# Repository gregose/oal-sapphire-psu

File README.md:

# oal-sapphire-psu
Transformer and rectifier board for RJM's Sapphire

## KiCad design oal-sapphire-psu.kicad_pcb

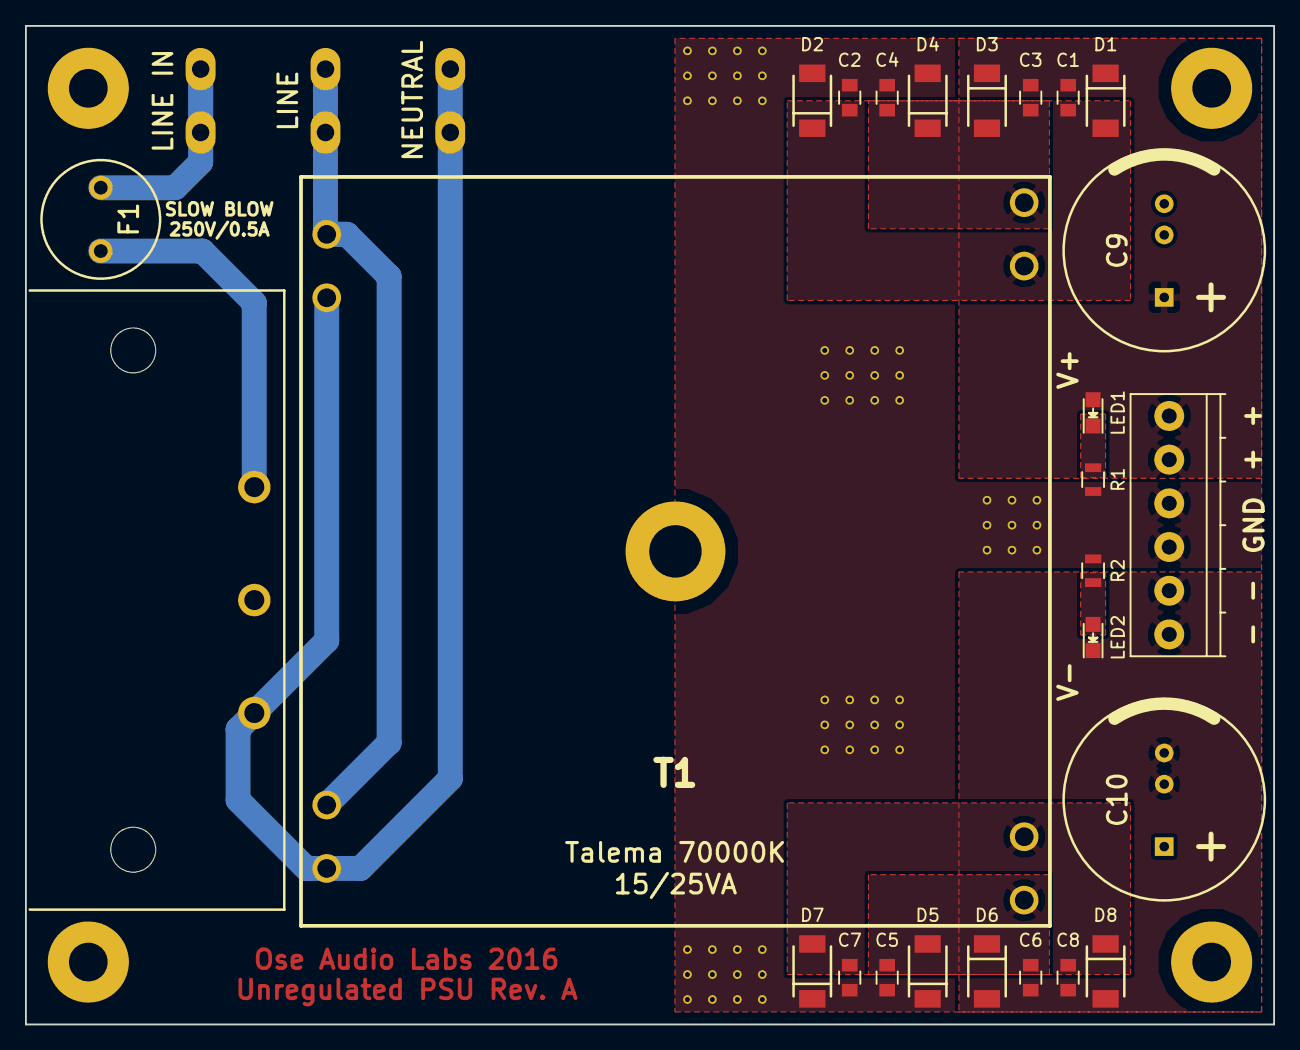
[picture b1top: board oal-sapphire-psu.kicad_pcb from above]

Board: 2 copper layers, 100.0 x 80.0 mm, 33 parts (0 on the bottom side), 13 nets.

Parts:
C1, C2, C3, C4, C5, C6, C7, C8: 0.1uF; C_0805
C9, C10: 4700uF; 25V-LYTIC-7.5-5-16mm
D1, D2, D3, D4, D5, D6, D7, D8: D; NXP-SOD128
F1: FUSE; SCHURTER_FMS250V
LED1: V+; LED_0805
LED2: V-; LED_0805
P1: 120V AC; Schurter_GSP1.8101.1
P2: LINE IN; FASTON_TAB
P3: LINE; FASTON_TAB
P4: NEUTRAL; FASTON_TAB
P7: OUTPUT; TerminalBlock_Pheonix_PT-3.5mm_6pol-Vertical
R1, R2: 680R; R_0805
T1: TALEMA-25VA/12V; TALEMA_70000K_15-25VA
X1, X2, X3, X4: MOUNTING_HOLE; MOUNTING_HOLE-M3

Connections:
GROUND: C2.1, C4.1, C5.2, C7.2, C9.2, C10.1, D2.2, D4.2, D5.1, D7.1, P7.3, P7.4, R1.1, R2.2
LINE: F1.1, P1.1
NEUTRAL: P1.3, P4.1, T1.3, T1.5
unnamed: C1.1, C2.2, D1.2, D2.1, T1.12
unnamed: C3.1, C4.2, D3.2, D4.1, T1.11
unnamed: C5.1, C6.2, D5.2, D6.1, T1.14
unnamed: C7.1, C8.2, D7.2, D8.1, T1.13
unnamed: F1.2, P2.1
unnamed: LED1.1, R1.2
unnamed: LED2.2, R2.1
unnamed: P3.1, T1.4, T1.6
V+: C1.2, C3.2, C9.1, D1.1, D3.1, LED1.2, P7.5, P7.6
V-: C6.1, C8.1, C10.2, D6.2, D8.2, LED2.1, P7.1, P7.2

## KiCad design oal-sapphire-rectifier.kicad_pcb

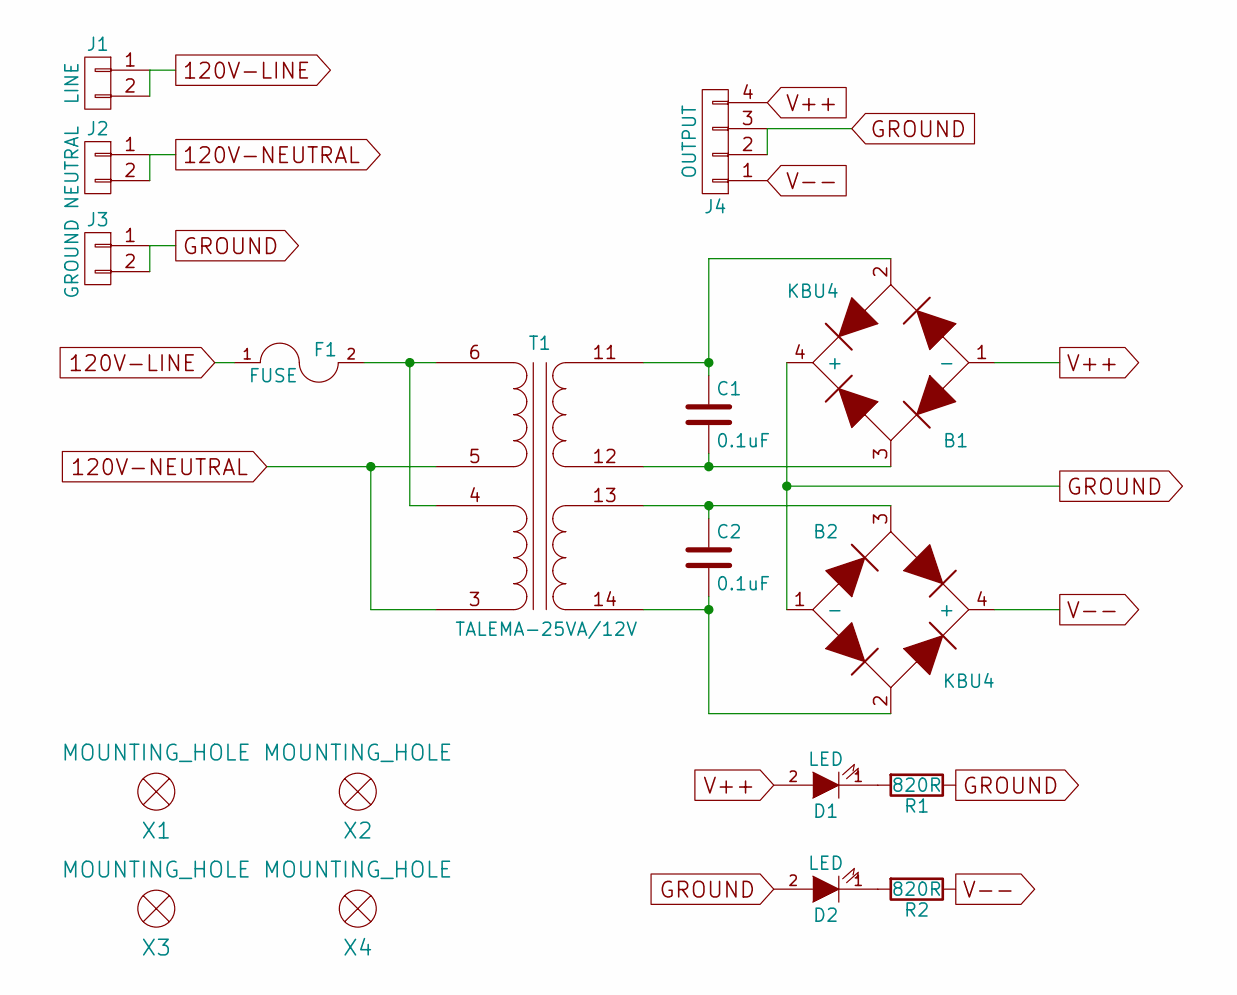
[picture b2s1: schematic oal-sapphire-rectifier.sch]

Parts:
B1, B2: KBU4; VISHAY-KBU4
C1, C2: 0.1uF; TDK-B32529-63VAC
D1, D2: LED; LED-3MM
F1: FUSE; LITTLEFUSE-560-TR5
J1: LINE; PHEONIX_SPT_5-2POS
J2: NEUTRAL; PHEONIX_SPT_5-2POS
J3: GROUND; PHEONIX_SPT_5-2POS
J4: OUTPUT; MSTBA-2.5_4-G
R1, R2: 820R; Resistor_Horizontal_RM10mm
T1: TALEMA-25VA/12V; TALEMA_70000K_15-25VA
X1, X2, X3, X4: MOUNTING_HOLE; MOUNTING_HOLE-M3

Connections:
120V-LINE: F1.1, J1.1, J1.2
120V-NEUTRAL: J2.1, J2.2, T1.3 (PRIMARY2-NODOT), T1.5 (PRIMARY1-NODOT)
GROUND: B1.4 (+), B2.1 (-), D2.2 (A), J3.1, J3.2, J4.2, J4.3, R1.1
unnamed: B1.2, C1.1, T1.11 (SECONDARY1-DOT)
unnamed: B1.3, C1.2, T1.12 (SECONDARY1-NODOT)
unnamed: B2.2, C2.2, T1.14 (SECONDARY2-NODOT)
unnamed: B2.3, C2.1, T1.13 (SECONDARY2-DOT)
unnamed: D1.1 (K), R1.2
unnamed: D2.1 (K), R2.2
unnamed: F1.2, T1.4 (PRIMARY2-DOT), T1.6 (PRIMARY1-DOT)
V++: B1.1 (-), D1.2 (A), J4.4
V--: B2.4 (+), J4.1, R2.1

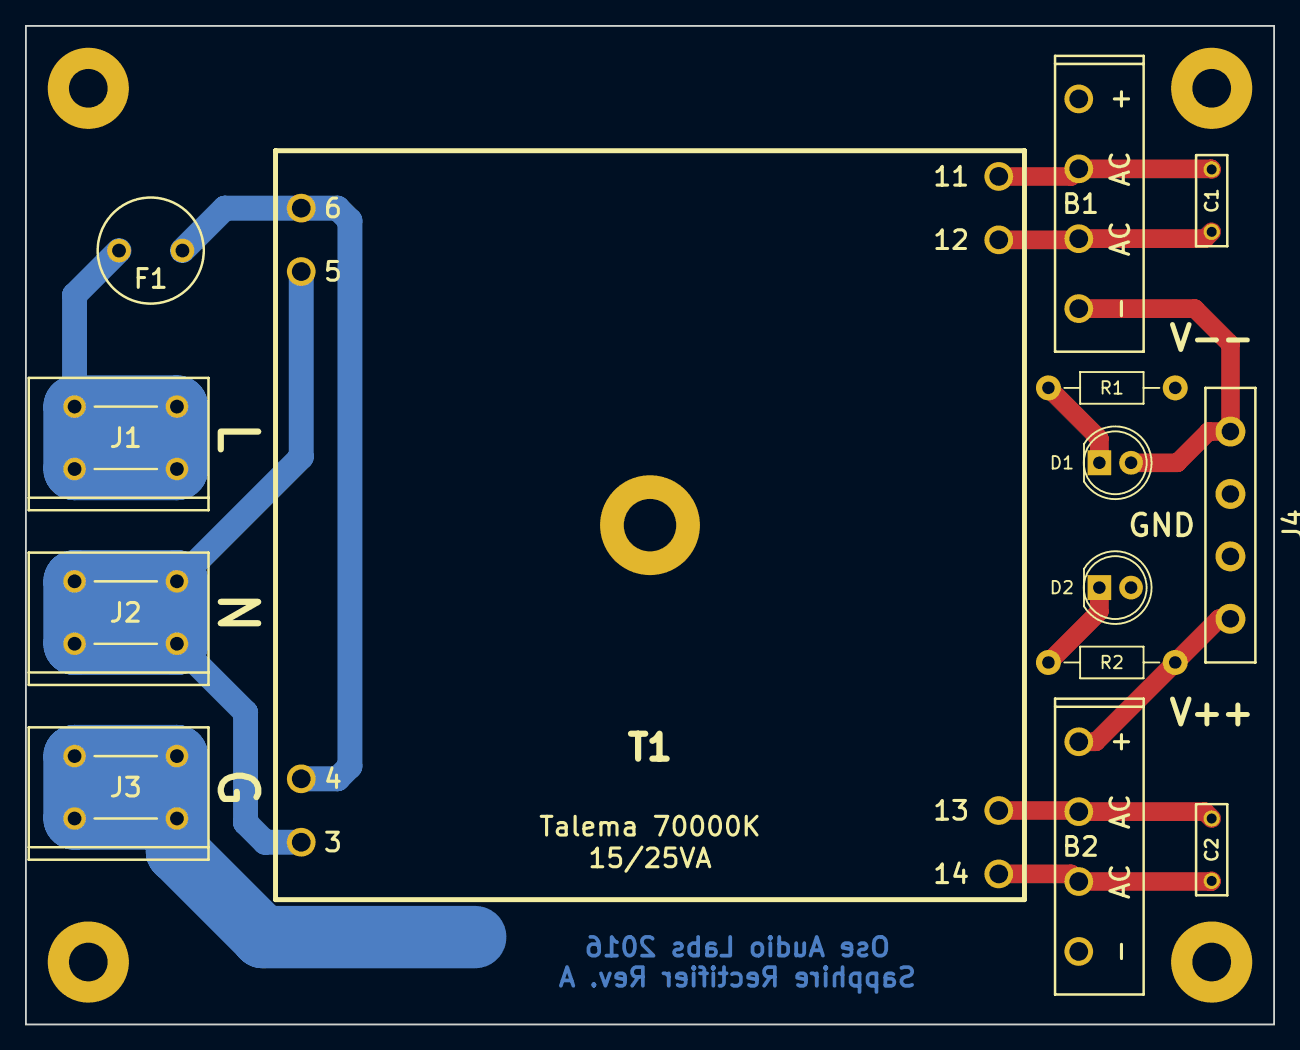
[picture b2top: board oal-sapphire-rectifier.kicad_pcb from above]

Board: 2 copper layers, 100.0 x 80.0 mm, 18 parts (0 on the bottom side), 12 nets.

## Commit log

2016-03-12 intial schematic commit
2016-03-13 initial component placement
2016-03-13 initial layout
2016-08-06 new layout
2016-08-07 silk screen cleanup
2016-08-08 updated layout
2016-08-09 route all smd w/ ground pours
2016-08-09 pad updates
2016-08-10 via stitching for ground plane
2016-08-10 docs
2016-08-10 stl board render
2016-08-10 freecad stl export doesnt work
2016-08-14 simplified 120v only layout
2016-08-15 120v only
2016-08-15 rev a fab
2016-08-15 rename gerb layers to be standard
